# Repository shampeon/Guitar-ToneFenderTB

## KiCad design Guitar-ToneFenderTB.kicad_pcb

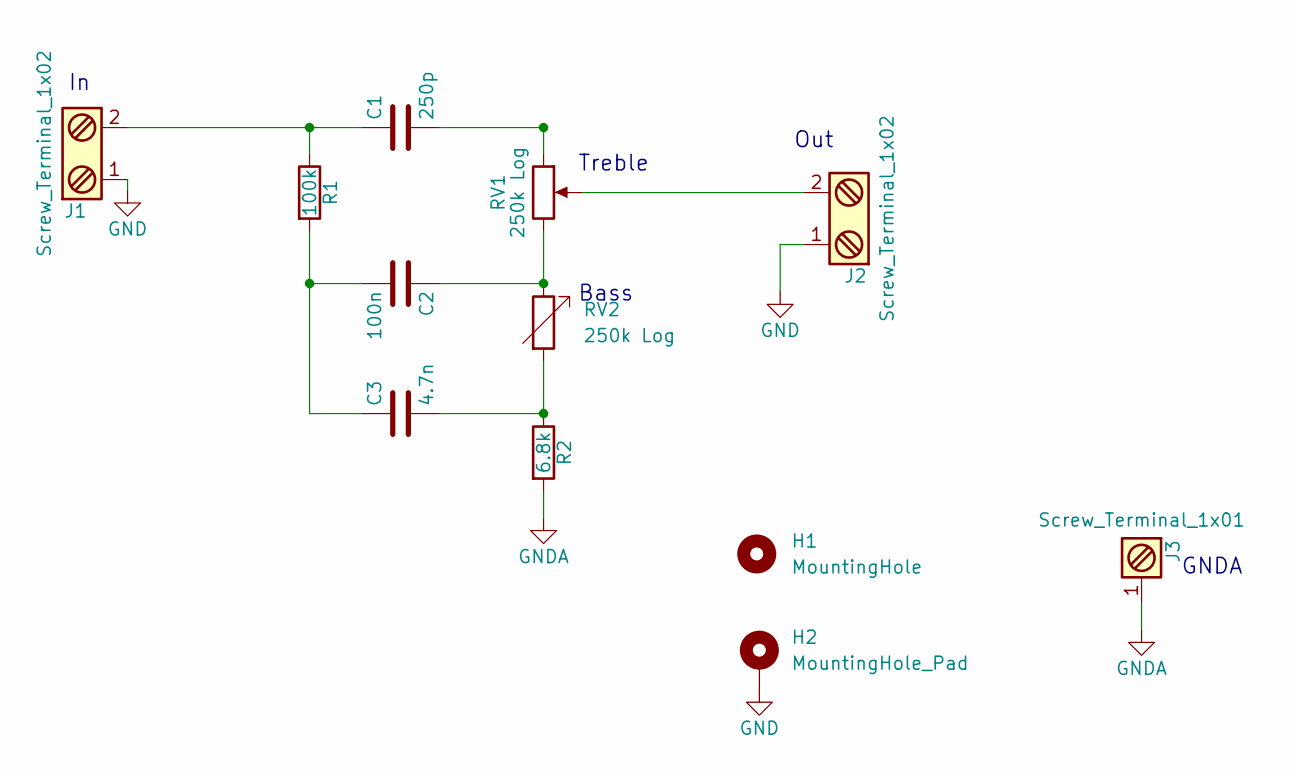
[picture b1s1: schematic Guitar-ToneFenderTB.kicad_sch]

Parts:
C1: 250p; C_Disc_D7.5mm_W5.0mm_P7.50mm
C2: 100n; C_Axial_L22.0mm_D9.5mm_P27.50mm_Horizontal
C3: 4.7n; C_Axial_L12.0mm_D6.5mm_P15.00mm_Horizontal
H1: MountingHole; MountingHole_3.2mm_M3
H2: MountingHole_Pad; MountingHole_3.2mm_M3_Pad
J1, J2: Screw_Terminal_1x02; PhoenixContact_MCV_1,5_2-G-5.08_1x02_P5.08mm_Vertical
J3: Screw_Terminal_1x01; SolderWire-0.75sqmm_1x01_D1.25mm_OD2.3mm
R1: 100k; R_Axial_DIN0414_L11.9mm_D4.5mm_P15.24mm_Horizontal
R2: 6.8k; R_Axial_DIN0414_L11.9mm_D4.5mm_P15.24mm_Horizontal
RV1: 250k Log; PhoenixContact_MCV_1,5_3-G-5.08_1x03_P5.08mm_Vertical; MPN 1729131
RV2: 250k Log; PhoenixContact_MCV_1,5_3-G-5.08_1x03_P5.08mm_Vertical

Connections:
GND: H2.1, J1.1, J2.1
GNDA: J3.1, R2.2
unnamed: C1.1, J1.2, R1.1
unnamed: C1.2, RV1.1
unnamed: C2.1, RV1.3, RV2.1
unnamed: C2.2, C3.1, R1.2
unnamed: C3.2, R2.1, RV2.2
unnamed: J2.2, RV1.2

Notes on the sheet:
Treble
Out
Bass
GNDA

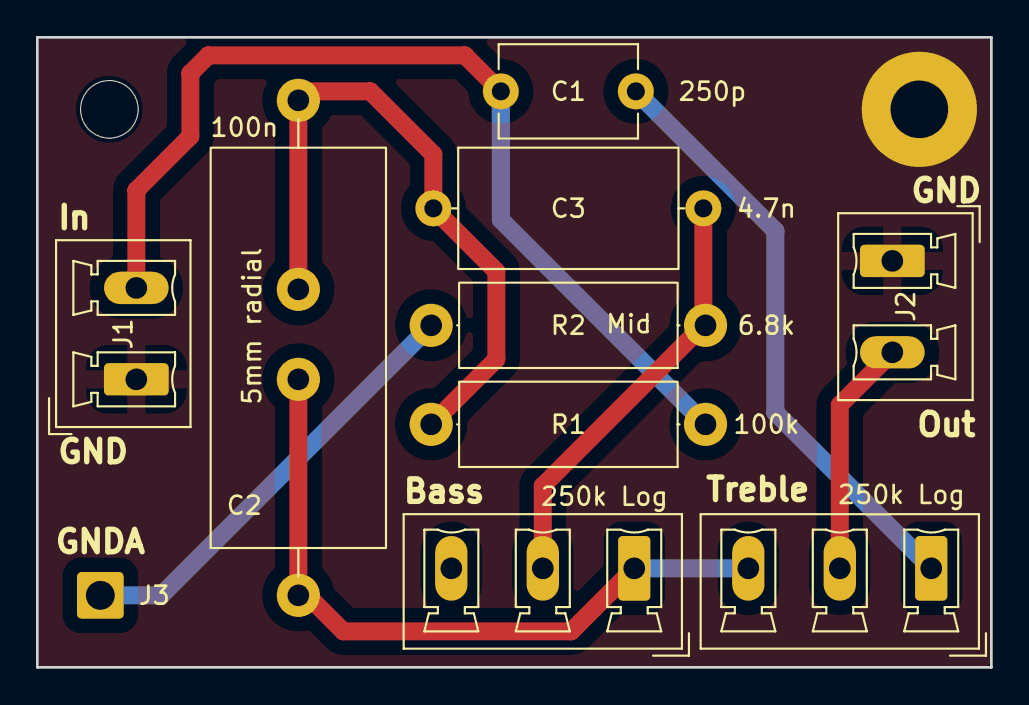
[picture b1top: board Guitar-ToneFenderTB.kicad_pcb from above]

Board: 2 copper layers, 53.0 x 35.0 mm, 12 parts (0 on the bottom side), 8 nets.

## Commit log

2025-08-08 Initial checkin.
2025-08-08 Adding .gitignore.
2025-08-08 Updated silkscreen text with C2 5mm spacing, and PCBWay product number code
2025-08-08 Ignore backups directory.
2025-08-08 Adjust placement of back silkscreen text.
2025-08-08 Adding Gerber ZIP.
2025-08-08 Ignore lock files.
2025-08-08 Removing previously committed backup zips.
2025-08-09 Fixed error in schematic, enlarged through holes for caps.
